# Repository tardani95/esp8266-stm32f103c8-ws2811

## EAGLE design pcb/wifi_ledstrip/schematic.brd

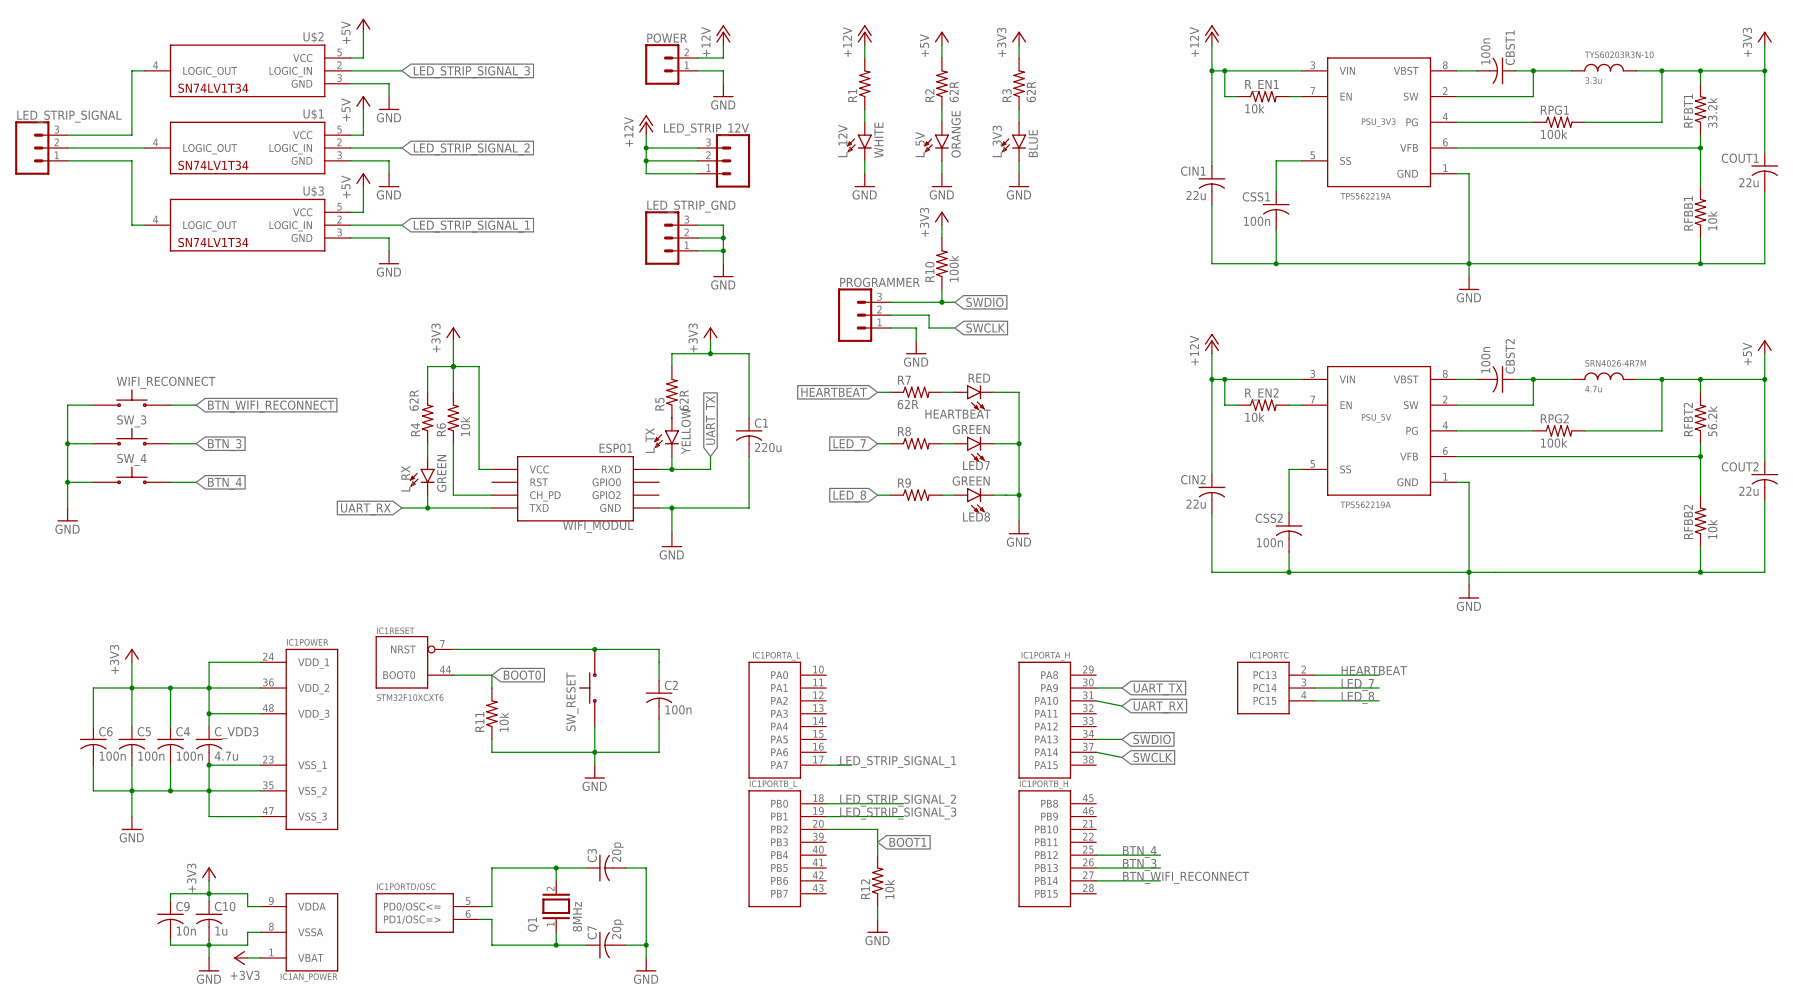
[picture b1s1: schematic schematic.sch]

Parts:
C1: 220u; C1206
C2, C4, C5, C6: 100n; C1206
C3, C7: 20p; C1206
C9: 10n; C1206
C10: 1u; C1206
CBST1, CBST2: 100n; C1206
CIN1, CIN2: 22u; C1206
COUT1, COUT2: 22u; C1206
CSS1, CSS2: 100n; C1206
C_VDD3: 4.7u; C1206
HEARTBEAT: RED; LED-1206
IC1: STM32F10XCXT6; TQFP48
LED7, LED8: GREEN; LED-1206
LED_STRIP_12V: CONN_03SCREW; SCREWTERMINAL-3.5MM-3
LED_STRIP_GND: CONN_03SCREW; SCREWTERMINAL-3.5MM-3
LED_STRIP_SIGNAL: CONN_03SCREW; SCREWTERMINAL-3.5MM-3
L_3V3: BLUE; LED-1206
L_5V: ORANGE; LED-1206
L_12V: WHITE; LED-1206
L_RX: GREEN; LED-1206
L_TX: YELLOW; LED-1206
POWER: CONN_025MM; SCREWTERMINAL-5MM-2
PROGRAMMER: CONN_03POLAR; MOLEX-1X3
PSU_3V3, PSU_5V: TPS562219A; SOT23-8L
Q1: 8MHz; QS
R1, R8, R9: R-US_R1206; R1206
R2, R3, R4, R5, R7: 62R; R1206
R6, R11, R12: 10k; R1206
R10: 100k; R1206
RFBB1, RFBB2: 10k; R1206
RFBT1: 33.2k; R1206
RFBT2: 56.2k; R1206
RPG1, RPG2: 100k; R1206
R_EN1, R_EN2: 10k; R1206
SRN4026-4R7M: 4.7u; SRN4026-4R7M
SW_3, SW_4: TACTILE_SWITCH_SIDETACTILE_SWITCH_SIDE; TACTILE_SWITCH_SIDE
SW_RESET: TACTILE_SWITCH_SIDETACTILE_SWITCH_SIDE; TACTILE_SWITCH_SIDE
TYS60203R3N-10: 3.3u; TYS60203R3N-10
U$1, U$2, U$3: SN74LV1T34; SOT-23-5
WIFI_MODUL: ESP01
WIFI_RECONNECT: TACTILE_SWITCH_SIDETACTILE_SWITCH_SIDE; TACTILE_SWITCH_SIDE

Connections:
+3V3: C1.1, C4.1, C5.1, C6.1, C9.1, C10.1, COUT1.1, C_VDD3.1, IC1.1 (VBAT), IC1.9 (VDDA), IC1.24 (VDD_1), IC1.36 (VDD_2), IC1.48 (VDD_3), R3.2, R4.2, R5.2, R6.2, R10.2, RFBT1.2, RPG1.2, TYS60203R3N-10.P$2 (2), WIFI_MODUL.VCC
+5V: COUT2.1, R2.2, RFBT2.2, RPG2.2, SRN4026-4R7M.P$3 (2), U$1.5 (VCC), U$2.5 (VCC), U$3.5 (VCC)
+12V: CIN1.1, CIN2.1, LED_STRIP_12V.1, LED_STRIP_12V.2, LED_STRIP_12V.3, POWER.2, PSU_3V3.3 (VIN), PSU_5V.3 (VIN), R1.2, R_EN1.1, R_EN2.1
BOOT0: IC1.44 (BOOT0), R11.2
BOOT1: IC1.20 (PB2), R12.2
BTN_3: IC1.26 (PB13), SW_3.P$5
BTN_4: IC1.25 (PB12), SW_4.P$5
BTN_WIFI_RECONNECT: IC1.27 (PB14), WIFI_RECONNECT.P$5
GND: C1.2, C2.2, C3.2, C4.2, C5.2, C6.2, C7.2, C9.2, C10.2, CIN1.2, CIN2.2, COUT1.2, COUT2.2, CSS1.2, CSS2.2, C_VDD3.2, HEARTBEAT.C, IC1.8 (VSSA), IC1.23 (VSS_1), IC1.35 (VSS_2), IC1.47 (VSS_3), LED7.C, LED8.C, LED_STRIP_GND.1, LED_STRIP_GND.2, LED_STRIP_GND.3, L_3V3.C, L_5V.C, L_12V.C, POWER.1, PROGRAMMER.1, PSU_3V3.1 (GND), PSU_5V.1 (GND), R11.1, R12.1, RFBB1.1, RFBB2.1, SW_3.P$3, SW_4.P$3, SW_RESET.P$5, U$1.3 (GND), U$2.3 (GND), U$3.3 (GND), WIFI_MODUL.GND, WIFI_RECONNECT.P$3
HEARTBEAT: IC1.2 (PC13), R7.1
LED_7: IC1.3 (PC14), R8.1
LED_8: IC1.4 (PC15), R9.1
LED_STRIP_SIGNAL_1: IC1.17 (PA7), U$3.2 (LOGIC_IN)
LED_STRIP_SIGNAL_2: IC1.18 (PB0), U$1.2 (LOGIC_IN)
LED_STRIP_SIGNAL_3: IC1.19 (PB1), U$2.2 (LOGIC_IN)
unnamed: LED_STRIP_SIGNAL.3, U$2.4 (LOGIC_OUT)
unnamed: LED_STRIP_SIGNAL.2, U$1.4 (LOGIC_OUT)
unnamed: LED_STRIP_SIGNAL.1, U$3.4 (LOGIC_OUT)
unnamed: L_12V.A, R1.1
unnamed: L_5V.A, R2.1
unnamed: L_3V3.A, R3.1
unnamed: L_RX.A, R4.1
unnamed: R6.1, WIFI_MODUL.CH_PD
unnamed: L_TX.A, R5.1
unnamed: HEARTBEAT.A, R7.2
unnamed: LED7.A, R8.2
unnamed: LED8.A, R9.2
unnamed: C2.1, IC1.7 (NRST), SW_RESET.P$3
unnamed: C3.1, IC1.5 (PD0/OSC<=), Q1.2
unnamed: C7.1, IC1.6 (PD1/OSC=>), Q1.1
unnamed: CBST1.2, PSU_3V3.8 (VBST)
unnamed: CBST1.1, PSU_3V3.2 (SW), TYS60203R3N-10.P$1 (1)
unnamed: CBST2.2, PSU_5V.8 (VBST)
unnamed: PSU_3V3.6 (VFB), RFBB1.2, RFBT1.1
unnamed: CBST2.1, PSU_5V.2 (SW), SRN4026-4R7M.P$2 (1)
unnamed: PSU_5V.6 (VFB), RFBB2.2, RFBT2.1
unnamed: PSU_3V3.7 (EN), R_EN1.2
unnamed: PSU_5V.7 (EN), R_EN2.2
N$PG1: PSU_3V3.4 (PG), RPG1.1
N$PG2: PSU_5V.4 (PG), RPG2.1
N$SS1: CSS1.1, PSU_3V3.5 (SS)
N$SS2: CSS2.1, PSU_5V.5 (SS)
SWCLK: IC1.37 (PA14), PROGRAMMER.2
SWDIO: IC1.34 (PA13), PROGRAMMER.3, R10.1
UART_RX: IC1.31 (PA10), L_RX.C, WIFI_MODUL.TX (TXD)
UART_TX: IC1.30 (PA9), L_TX.C, WIFI_MODUL.RX (RXD)

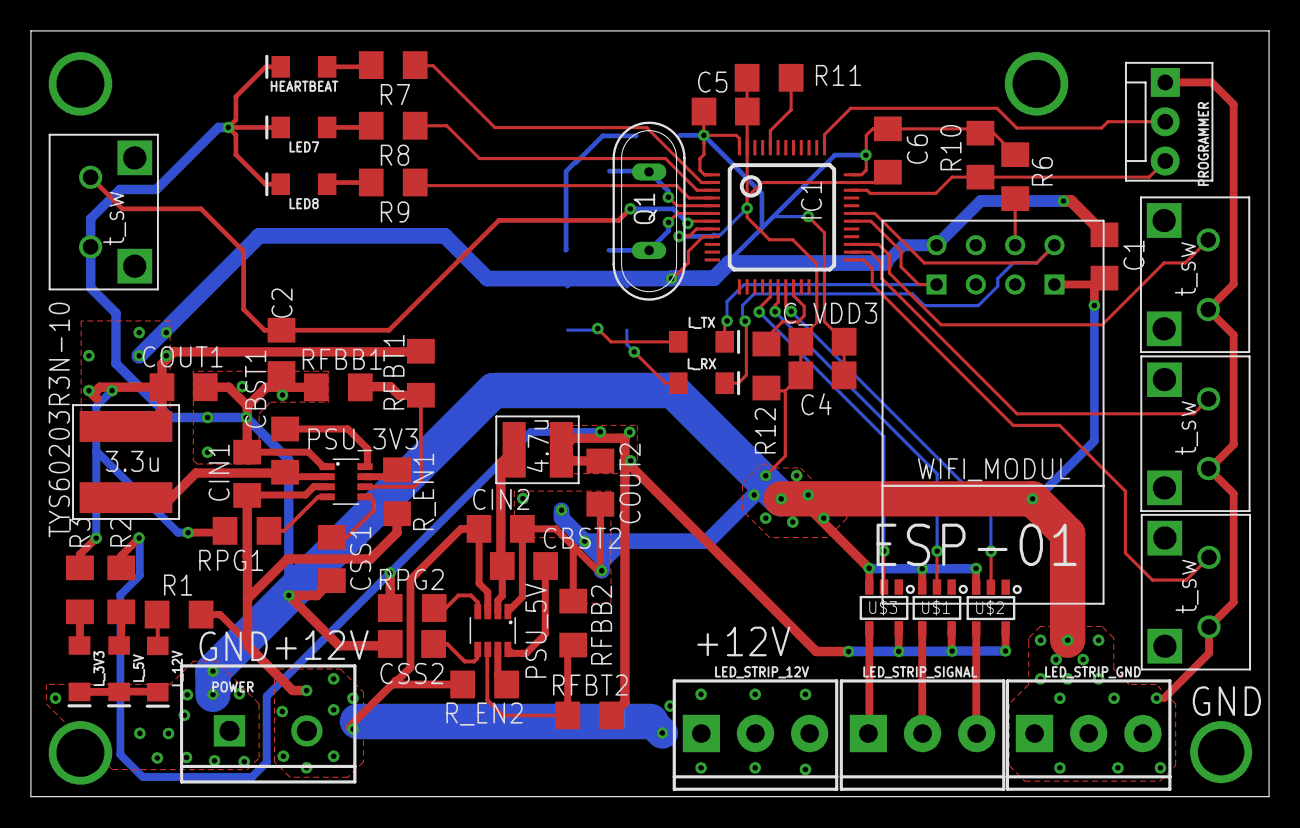
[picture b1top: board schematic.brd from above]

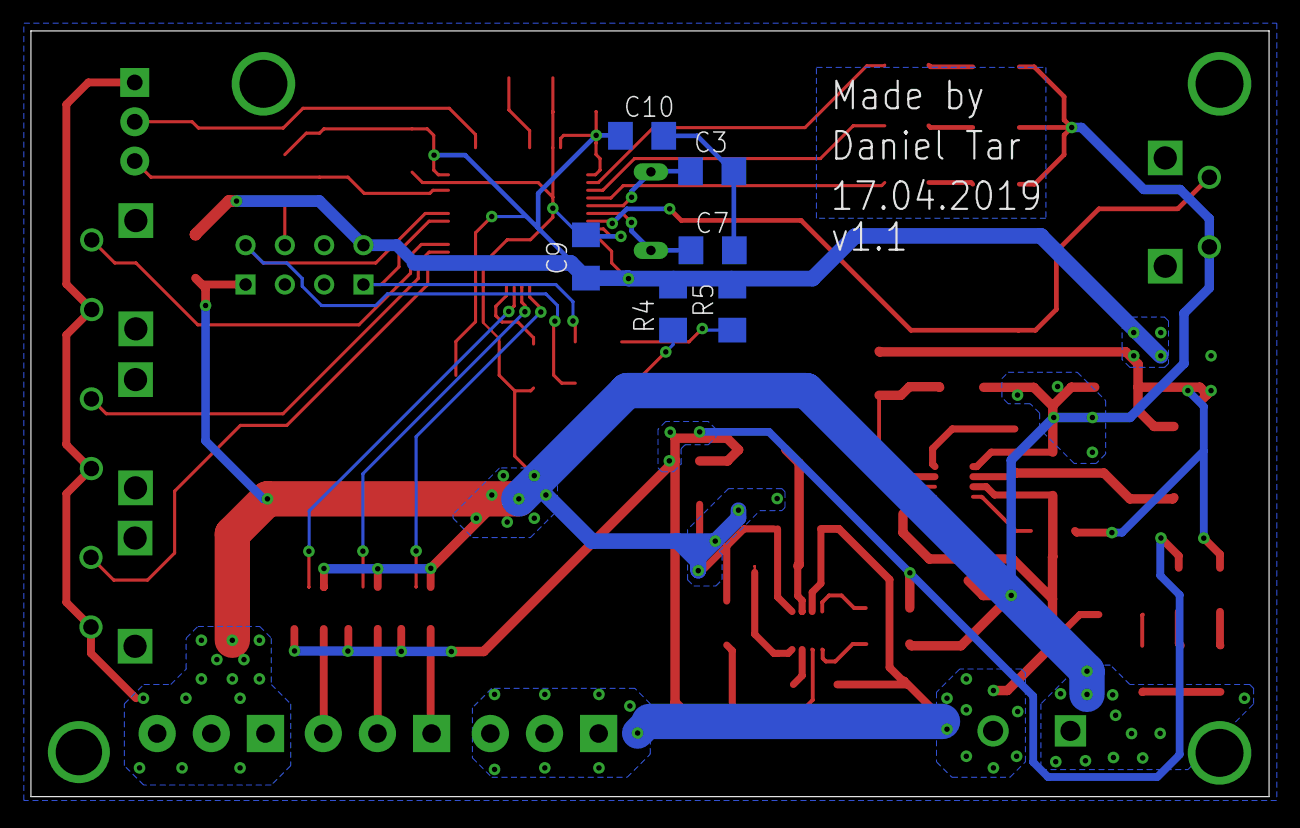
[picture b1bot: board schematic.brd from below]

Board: 2 copper layers, 80.0 x 49.5 mm, 65 parts (6 on the bottom side), 46 nets.

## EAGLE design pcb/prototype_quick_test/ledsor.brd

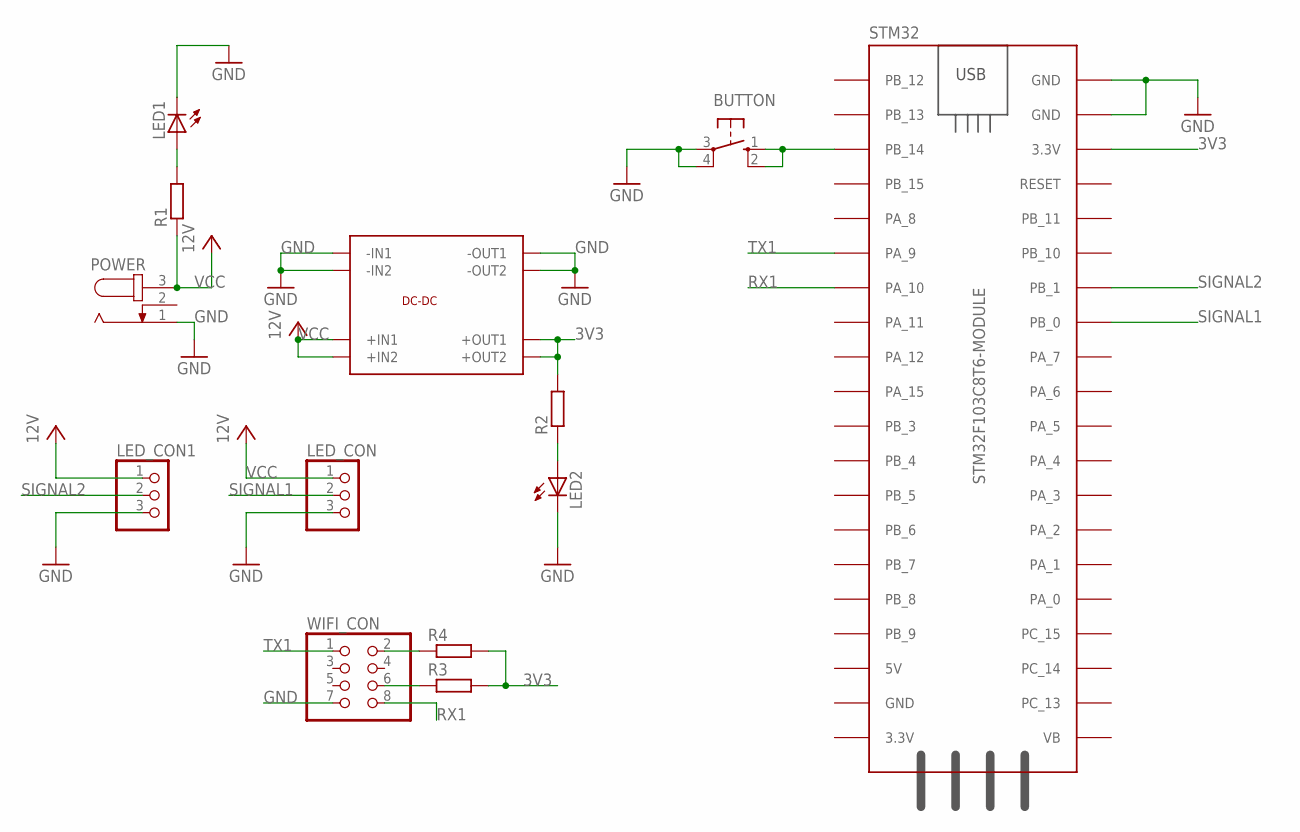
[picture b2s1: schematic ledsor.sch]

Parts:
BUTTON: 10-XX; B3F-10XX
DC-DC: SDVR_SMALL
LED1, LED2: LED5MM
LED_CON, LED_CON1: PINHD-1X3; 1X03
POWER: JACK-PLUG1; SPC4078
R1, R2, R3, R4: R-EU_0204/7; 0204/7
STM32: STM32F103C8T6-MODULE
WIFI_CON: PINHD-2X4; 2X04

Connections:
3V3: DC-DC.P$7 (+OUT1), DC-DC.P$8 (+OUT2), R2.2, R3.2, R4.2, STM32.3.3V_2 (3.3V)
GND: BUTTON.3, BUTTON.4 (P1), DC-DC.P$1 (-IN1), DC-DC.P$2 (-IN2), DC-DC.P$5 (-OUT1), DC-DC.P$6 (-OUT2), LED1.K (C), LED2.K (C), LED_CON.3, LED_CON1.3, POWER.1, STM32.GND_2 (GND), STM32.GND_3 (GND), WIFI_CON.7
unnamed: LED1.A, R1.2
unnamed: R3.1, WIFI_CON.6
unnamed: LED2.A, R2.1
unnamed: R4.1, WIFI_CON.2
unnamed: BUTTON.1 (S), BUTTON.2 (S1), STM32.PB_14
RX1: STM32.PA_10, WIFI_CON.8
SIGNAL1: LED_CON.2, STM32.PB_0
SIGNAL2: LED_CON1.2, STM32.PB_1
TX1: STM32.PA_9, WIFI_CON.1
VCC: DC-DC.P$3 (+IN1), DC-DC.P$4 (+IN2), LED_CON.1, LED_CON1.1, POWER.3, R1.1

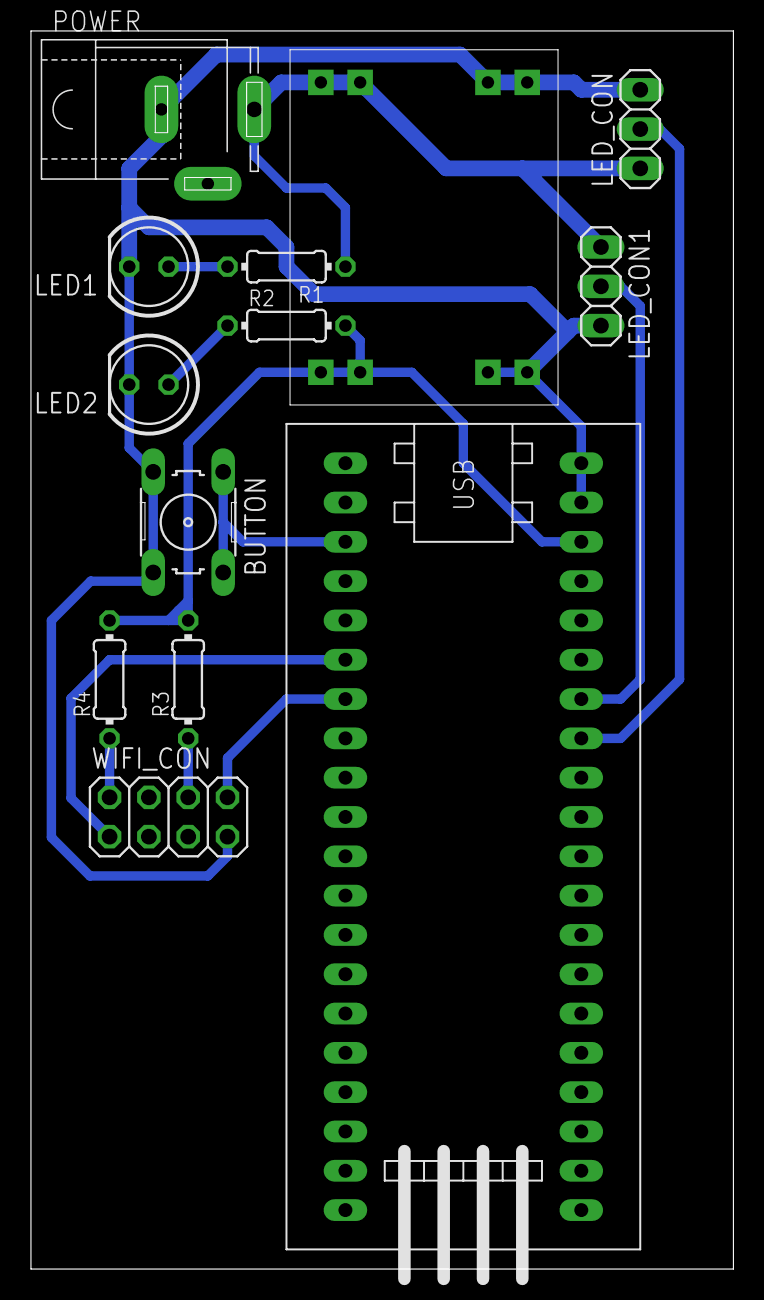
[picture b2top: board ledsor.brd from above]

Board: 2 copper layers, 45.4 x 80.0 mm, 13 parts (0 on the bottom side), 12 nets.

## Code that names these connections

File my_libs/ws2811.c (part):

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/******************************************************************************/

/**
 * @brief  This function initialize the led strip signals on PA7, PB0, PB1
 * @param  GPIO_InitTypeDef variable address
 * @retval None
 */
void InitGPIO_LSSs(GPIO_InitTypeDef* GPIO_InitStructure) {

	uint16_t ledstrip_signal1 = GPIO_Pin_7; /* PA7  */
	uint16_t ledstrip_signal2 = GPIO_Pin_0; /* PB0  */
	uint16_t ledstrip_signal3 = GPIO_Pin_1; /* PB1  */

	RCC_APB2PeriphClockCmd(
	RCC_APB2Periph_GPIOA | RCC_APB2Periph_GPIOB | RCC_APB2Periph_AFIO, ENABLE);

	/* PA7  */
	GPIO_InitStructure->GPIO_Pin = ledstrip_signal1;
	GPIO_InitStructure->GPIO_Mode = GPIO_Mode_AF_PP;
	GPIO_InitStructure->GPIO_Speed = GPIO_Speed_10MHz;
	GPIO_Init(GPIOA, GPIO_InitStructure); /* !GPIOA! */

	/* PB0 & PB1  */
	GPIO_InitStructure->GPIO_Pin = ledstrip_signal2 | ledstrip_signal3;
	GPIO_InitStructure->GPIO_Mode = GPIO_Mode_AF_PP;
	GPIO_InitStructure->GPIO_Speed = GPIO_Speed_10MHz;
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#ifdef DEBUG_PINS_ON
	RCC_APB2PeriphClockCmd(RCC_APB2Periph_GPIOC, ENABLE);

	/* PC14 & PC15  */
	GPIO_InitStructure->GPIO_Pin = GPIO_Pin_14 | GPIO_Pin_15;
	GPIO_InitStructure->GPIO_Mode = GPIO_Mode_Out_PP;
	GPIO_InitStructure->GPIO_Speed = GPIO_Speed_10MHz;
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
/**
 * @brief  This function initialize the DMA controller for the TIM3 OC values
 * 		from CH2 to CH4 (PA7 PB0 PB1)
 * 		Initialize TIMx (TIM3) first
 * @param  DMA_InitTypeDef variable
 * @param  ledstrip_transmit_dma_buffer - uint8_t[] buffer to send
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
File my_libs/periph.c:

/*
 * periph.c
 *
 *  Created on: Apr 25, 2018
 *      Author: tar
 */

/******************************************************************************/
/*                               Includes									  */
/******************************************************************************/
#include "periph.h"
#include "eeprom.h"
#include "ws2811.h"
#include "ws2811_util.h"
/******************************************************************************/
/*                               Variables									  */
/******************************************************************************/
uint16_t led_pin = GPIO_Pin_13; /* PC13 */
uint16_t button_pin0 = GPIO_Pin_12; /* PB12 */
uint16_t button_pin1 = GPIO_Pin_13; /* PB13 */
uint16_t button_pin2 = GPIO_Pin_14; /* PB14 */

__IO uint8_t button0_state = STD_MODE;
__IO uint8_t button_palette_pointer = 0;
__IO uint8_t button_palette_size;

uint16_t VirtAddVarTab2[] = { 0x0000, 0x0001, 0x0002, 0x0003, 0x0004, 0x0005 };

/******************************************************************************/
/*            			         Functions                                    */
/******************************************************************************/

void Init_EEPROM() {
	/* Unlock the Flash Program Erase controller */
	FLASH_Unlock();
	/* EEPROM Init */
	EE_Init();
	/* Lock the Flash Program Erase controller */
	FLASH_Lock();
}

/**
 * @brief  This function initialize the LED on PC13 pin
 * @param  GPIO_InitTypeDef variable address
 * @retval None
 */
void InitGPIO_LED(GPIO_InitTypeDef* GPIO_InitStructure) {
	RCC_APB2PeriphClockCmd(RCC_APB2Periph_GPIOC, ENABLE);

	GPIO_StructInit(GPIO_InitStructure);

	GPIO_InitStructure->GPIO_Mode = GPIO_Mode_Out_PP;
	GPIO_InitStructure->GPIO_Pin = led_pin;
	GPIO_InitStructure->GPIO_Speed = GPIO_Speed_2MHz;
	GPIO_Init(GPIOC, GPIO_InitStructure);
}

/**
 * @brief  This function initialize the button on PB12,PB13,PB14 pin
 * @param  GPIO_InitTypeDef variable address
 * @retval None
 */
void InitGPIO_BTN(GPIO_InitTypeDef* GPIO_InitStructure) {
	RCC_APB2PeriphClockCmd(RCC_APB2Periph_GPIOB | RCC_APB2Periph_AFIO, ENABLE);

	GPIO_StructInit(GPIO_InitStructure);

	GPIO_InitStructure->GPIO_Mode = GPIO_Mode_IPU;
	GPIO_InitStructure->GPIO_Speed = GPIO_Speed_2MHz;

	GPIO_InitStructure->GPIO_Pin = button_pin0;
	GPIO_Init(GPIOB, GPIO_InitStructure);

	GPIO_InitStructure->GPIO_Pin = button_pin1;
	GPIO_Init(GPIOB, GPIO_InitStructure);

	GPIO_InitStructure->GPIO_Pin = button_pin2;
	GPIO_Init(GPIOB, GPIO_InitStructure);
}

/**
 * @brief  This function initialize the external interrupt on PB12,PB13,PB14 and sets the nested vectored interrupt controller
 * @param  EXTI_InitStructure: pointer to a EXTI_InitTypeDef structure which will
 *         be initialized.
 *         NVIC_InitStructure: pointer to a NVIC_InitTypeDef structure which will
 *         be initialized.
 * @retval None
 */
void InitEXTI_BTN(EXTI_InitTypeDef* EXTI_InitStructure,
		NVIC_InitTypeDef* NVIC_InitStructure) {

	NVIC_PriorityGroupConfig(NVIC_PriorityGroup_4);
	/* NVIC_PriorityGroup_4: 4 bits for pre-emption priority
	 *                       0 bits for subpriority*
	 */

	NVIC_InitStructure->NVIC_IRQChannel = EXTI15_10_IRQn;
	NVIC_InitStructure->NVIC_IRQChannelCmd = ENABLE;
	NVIC_InitStructure->NVIC_IRQChannelPreemptionPriority = 0x0F;
	NVIC_InitStructure->NVIC_IRQChannelSubPriority = 0x0F;
	NVIC_Init(NVIC_InitStructure);

	EXTI_StructInit(EXTI_InitStructure);

	GPIO_EXTILineConfig(GPIO_PortSourceGPIOB, GPIO_PinSource12);
	GPIO_EXTILineConfig(GPIO_PortSourceGPIOB, GPIO_PinSource13);
	GPIO_EXTILineConfig(GPIO_PortSourceGPIOB, GPIO_PinSource14);

	EXTI_InitStructure->EXTI_Line = EXTI_Line12 | EXTI_Line13 | EXTI_Line14;
	EXTI_InitStructure->EXTI_Mode = EXTI_Mode_Interrupt;
	EXTI_InitStructure->EXTI_Trigger = EXTI_Trigger_Falling;
	EXTI_InitStructure->EXTI_LineCmd = ENABLE;
	EXTI_Init(EXTI_InitStructure);


	button_palette_pointer = 0;
	if (button0_state) {
		button_palette_size = rainbow[0];
		fillSolid(colorHexToRGB(rainbow[1]));
	} else {
		button_palette_size = PALETTES_SIZE;
		fillPattern(4); /*party palette*/
	}

//	GPIO_EXTILineConfig(GPIO_PortSourceGPIOB, GPIO_PinSource13);
//
//	EXTI_InitStructure->EXTI_Line = EXTI_Line13;
//	EXTI_InitStructure->EXTI_Mode = EXTI_Mode_Interrupt;
//	EXTI_InitStructure->EXTI_Trigger = EXTI_Trigger_Falling;
//	EXTI_InitStructure->EXTI_LineCmd = ENABLE;
//	EXTI_Init(EXTI_InitStructure);
//
//	GPIO_EXTILineConfig(GPIO_PortSourceGPIOB, GPIO_PinSource14);
//
//	EXTI_InitStructure->EXTI_Line = EXTI_Line14;
//	EXTI_InitStructure->EXTI_Mode = EXTI_Mode_Interrupt;
//	EXTI_InitStructure->EXTI_Trigger = EXTI_Trigger_Falling;
//	EXTI_InitStructure->EXTI_LineCmd = ENABLE;
//	EXTI_Init(EXTI_InitStructure);

}

void EXTI15_10_IRQHandler() {

	if (SET == EXTI_GetITStatus(EXTI_Line12)) {
		button0_state = !button0_state;

		button_palette_pointer = 0;
		if (button0_state) {
			button_palette_size = rainbow[0];
			fillSolid(colorHexToRGB(rainbow[1]));
		} else {
			button_palette_size = PALETTES_SIZE;
			fillPattern(4); /*party palette*/
		}

		if ((GPIOB->IDR & GPIO_Pin_14)) {
			GPIOC->ODR |= GPIO_Pin_13; /* led not light */
			//GPIOC->ODR |= GPIO_Pin_15;
		} else {
			GPIOC->ODR &= (~GPIO_Pin_13); /* led light */
			//GPIOC->ODR &= (~GPIO_Pin_15);
		}

		EXTI_ClearITPendingBit(EXTI_Line12);
	}

	if (SET == EXTI_GetITStatus(EXTI_Line13)) {
		button_palette_pointer++;

		if (button0_state) {
			fillSolid(
					colorHexToRGB(
							rainbow[(button_palette_pointer
									% button_palette_size) + 1]));
		} else {
			fillPattern(button_palette_pointer % button_palette_size);
		}

		EXTI_ClearITPendingBit(EXTI_Line13);
	}

	if (SET == EXTI_GetITStatus(EXTI_Line14)) {
		button_palette_pointer--;

		if (button0_state) {
//			if (button_palette_pointer < 1) {
//				button_palette_pointer = button_palette_size - 1;
//			}

			fillSolid(
					colorHexToRGB(
							rainbow[(button_palette_pointer
									% button_palette_size) + 1]));
		} else {
//			if (button_palette_pointer > button_palette_size) {
//				button_palette_pointer = button_palette_size - 1;
//			}
			fillPattern(button_palette_pointer % button_palette_size);
		}

		EXTI_ClearITPendingBit(EXTI_Line14);
	}

	refreshLedStrip();
}

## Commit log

2018-04-09 auto generated main.c file cleaned
2018-04-22 peripheral header files commented out - put these into main.c
2018-04-22 reading a button input and control a led
2018-04-22 led controll with a button - comments added
2018-04-22 .gitignore added
2018-04-22 gpio init - by iniputs the gpio speed unrelevant
2018-04-22 gpio read with interrupt
    modifiing pc14, pc15 according to pb14 input
    the prell effect - need to be corrected
2018-04-22 doc files added
    datasheets, programming manual, reference manual
2018-04-23 led control with interrupt
2018-04-24 ledstrip test - 800[kHz] - full 1 bit
2018-04-24 delayMicroSec function added for testing purposes
2018-04-24 save working settings
2018-04-24 pwm line added for external interrupt detection
2018-04-24 pwm 16bit High 8bit Low - rising edge
2018-04-24 theoretical functioning pwm signal to the led
2018-04-25 preload register for timer enabled
2018-04-25 new library added
2018-04-25 new library structure - it is compiling
    because I put the header and the c file into the src directory it is not compliled
    I added also into the build configurations
2018-04-25 my ledstrip work on 400[kHz] frequency - works
2018-04-25 quick fix - fill up the unused led with zeros to see the change
2018-04-26 minior changes - 400[kHz] + 800[kHz] modes added
2018-04-26 test with 2 led strip - logic shifter needed
    led number, led to light up defines added
    by the end of the 2nd strip the color is changing - logic level shifter needed or/and better power supply needed
2018-04-26 look_up_table_added - it slips 1 step
2018-04-26 slip fixed - lookup table converted to BRG values
2018-04-26 animation added in main.c
2018-04-26 timing trimmed
2018-04-26 animation function added in periph lib
    todo reorganize program stucture
2018-04-26 function light_up_from-to added - flickers last ledif the color has blue
2018-04-29 datasheets and at commands manual added to main.c
2018-04-30 uart init and first char readed the rest is not need to be fixed
2018-04-30 reading rx data into an array
2018-04-30 automatically starts the upd packet listening on port 1302
2018-04-30 stm32f103_ws2811 project pulled
2018-04-30 project compiling - updateing color according to the sent - todo: DMA
2018-04-30 test with two ledstrip
2018-05-05 the microprocessor drives two ledstrips parallel together on pb0,pb1
2018-05-05 prototype pcb design
2018-05-15 increased startup time for the esp8266 - a bit code cleanup
2018-05-15 documentation added
2018-05-15 debug directory removed
2018-05-23 comments fixed
2018-05-23 documentation
2018-05-23 documentation 3 pages
2018-05-23 uart gpio init function added - javadoc comments fixed
2018-05-23 linux elf file added
2018-05-23 doc fixed
2018-05-24 pdf updated
2018-05-24 pcb images added
2018-05-24 tex updated
2018-05-24 pdf finished
2018-05-24 main cleaned up
2018-05-30 uart rx mode changed to IPU - internal pull up
2018-05-30 dma irq handlers added
2018-05-30 empty dma irq handlers with description added
2018-05-30 header file includes updated - dma added
2018-05-30 nvic uart tx init function added
2018-05-30 includes moved to periph.h
2018-05-30 init dma functions added
2018-05-31 usart tx functions with dma ch4 - issue: usart rx not working
2018-06-01 uart with dma working - startup time set for esp8266 module
2018-06-01 timer3 dma init functions added
2018-06-01 timer3 with dma working
2018-06-02 multi channel pwm with dma basic functioning
2018-06-02 continously updating ledstrip
2018-06-07 esp lib files added
2018-06-15 esp lib files updated
2018-06-15 includes and function declarations added
2018-06-16 minior change in the header file
2018-06-16 function definitions added
2018-06-16 dma interrupt function callbacks added
2018-06-16 dma request irq-s callback removed from interrupt include
2018-06-16 esp functions removed from periph lib
2018-06-16 esp lib works - todo callback function on reception
2018-06-16 callback functions prepared
2018-06-16 callback function works with main
2018-06-16 code cleanup and function pointer fix
2018-06-16 ws2811 lib files added
2018-06-17 restructured folder system - compiler settings changed!
2018-06-17 util ilb added - delay functions
2018-06-17 util lib included
2018-06-17 function names updated according to util lib, function brief extended
2018-06-17 callback typedef moved to util.h
2018-06-17 debug purpose timer stopping functions added
2018-06-17 function declarations added
2018-06-17 variables added, gpio init function added
2018-06-17 dma initialization function added
2018-06-17 timer initialization functions added
2018-06-18 ledstrip functions moved to ws2811 lib - works with some glitches
2018-06-18 dma handler moved to ws2811 lib
2018-06-18 esp8266 and ws2811 init added
2018-06-18 uart array init moved here from main
2018-06-18 signal level high glitch fixed
2018-06-18 main prepared to animation looping
2018-06-18 solid animation fix
2018-06-19 clear and fill up dma buffer functions added
2018-06-19 tipo fix
2018-06-19 dma double buffering - this buffer size seems small
2018-06-19 issue - external interrupt callback called continously
2018-06-19 in main debug off, in ws2811 debug on
2018-06-19 issue identified - buffer handling slow
2018-06-19 fill_up function and data structure slow -> restructuring
2018-06-19 BRG stucture created with functions
2018-06-19 FillUp_DMA_HalfBuffer_BGR_map function fix
2018-06-19 FillUp_DMA_HalfBuffer_BGR_map speed up - still not enough
2018-06-19 works with O3 optimization - init dma buffer function fix
2018-06-19 works with optimization (O1, O2, O3, Og) - init dma buffer function fix
2018-06-19 quick change to work with network commands
2018-06-19 gamma correction fix
2018-06-21 pixel frame explaining exel file
2018-06-21 lib works with color palettes, comments added
2018-06-21 volatile warning fixed
2018-06-22 init dma buffer function fixed - init pixelmap function improved
2018-06-22 testing with different palettes - seems good
2018-06-22 gamma correction turned on
2018-06-22 parallel ledstrip signal slip fix
2018-06-22 improved callback function
2018-06-22 library template added
2018-06-22 color palettes header added
2018-06-22 unnecessary functions deleted
2018-06-23 color_palette lib extended
2018-06-23 new pixel_map, functions and defines
2018-06-23 template functions and meteorRain effect added to util library
2018-06-23 new dma buffer fillup method
2018-06-24 fillPattern() function added
2018-06-24 getPixelColorHex() function and typo fix, dma buffer works with pixel_map
2018-06-24 gitignore updated
2018-06-24 testing meteorRain anim
2018-06-24 color palettes and meteorRain animation works
2018-06-25 unnecessary functions removed, comments and setters and getters added
2018-06-25 functions definitions added
2018-06-25 testing ws2811 util library
2018-06-25 typo fix
2018-06-25 unnecessary funtcions removed
2018-06-25 comments added
2018-06-25 fade in fade out animation added
2018-06-25 old exti functions removed
2018-06-25 testing fade in fade out anim
2018-06-25 fade in fade out anim time constants trimmed
2018-06-25 typedef not found fixed
2018-06-25 cleaned up a littlebit
2018-06-25 millis and getsystickcount functions added
2018-06-25 strobe and bouncing balls animation added
2018-06-25 strobe - ok, todo: bouncing balls need to be fixed
2018-06-29 animations removed from main while loop startup time set
2018-07-15 800kHz mode set
2018-07-24 400kHz mode restored
2018-07-24 pcb design files added
2018-07-24 webench boms, schematic and board designs added
2018-07-24 main parts added
2018-07-24 mikrocontroller capacitances, boot pins, reset button added
2018-07-26 xtal added and microcontroller pins connected - psu missing
2018-07-26 parts added, psu symbols fixed
2018-07-27 datasheets added
2018-07-27 psu 5v half ready
2018-07-27 psu 5v and 3v3 ready
2018-07-27 psu fixed
2018-07-27 final size set
2018-07-30 beta pcb - resistor values need to be calculated
2018-07-30 libraries moved to local eagle lib folder
2018-07-30 new gitignore
2018-07-30 gerber files exported
2018-07-30 Auto stash before merge of "pcb_design" and "origin/pcb_design"
2018-09-07 gerber files created, pcb arrived
2018-09-25 electric parts arrived - pcb soldered
2018-09-25 pcb tested - with 800kHz mode strip
2018-09-30 pcb fix - boot1 pin pulled to gnd
2018-09-30 pcb fix - two more gnd polygon added
2018-10-11 atolic studio project settings added
2018-10-14 gitignore cleaned up
2018-10-14 pcb fixed - 2 wires were mixed up - bigger capacitance to SS pin
2018-10-14 capacitor moved a bit
2018-10-14 gerber files added
2018-10-22 bom updated - pcb library updated
2018-10-22 minor security check
2018-10-23 eeprom lib added
2018-10-23 rw of offset and length variables
2018-10-23 prepairing for changing offset - length values per ledstrip
2018-10-23 partial lightning - offset..length values added - rw from/to eeprom
2018-10-23 clear pixelmap function added
2018-11-05 pcb updated with leds
2018-11-05 initial fill pattern replaced with initial color
2018-11-10 o3 optimization enabled
2018-11-25 ledstrip configuration updated - schematic attributes moved - libraries updated
2019-04-08 color palette mode added
2019-04-08 the blue and green values by the new ledstrip is exchanged
2019-04-17 multiple exti lines in irq not working
2019-04-17 pcb ground plane style changed to solid
2019-04-18 interrrupt handler fix
2019-04-18 buttons IRQ handler moved to periph lib + array size initialization

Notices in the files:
parts and their libraries:
SparkFun-Connectors: Licensing: Creative Commons ShareAlike 4.0 International - https://creativecommons.org/licenses/by-sa/4.0
